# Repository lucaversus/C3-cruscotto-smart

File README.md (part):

# Cruscotto C3+AI

> **Data Logger in standby dal 02/11/2026 fino a nuovo ordine dell'utente (D-064)**, acquisti compresi
> (D1 P6KE33A non si ordina). Stato al blocco: modulo K-line montato e provato a banco (KL-M001, KL-M002);
> materiale arrivato e non montato a disposizione degli altri progetti nel magazzino condiviso.
> **In standby anche la scheda madre del cruscotto** (D-064): carrello svuotato e pezzi riservati liberati.
> Dettagli nel [registro moduli](data-logger/docs/verifiche-moduli.md).

## Fonti del progetto — consultazione obbligatoria

Prima di acquisti, firmware, schemi o collegamenti leggere questa sezione,
[l'inventario hardware](data-logger/docs/hardware-inventory.md),
[lo stato del Data Logger](data-logger/README.md) e la
[procedura di aggiornamento](data-logger/docs/procedura-progetto.md).
Le istruzioni per gli agenti sono in [AGENTS.md](AGENTS.md).
Per iniziare da un clone nuovo, su un altro PC o con un altro agente, seguire
[CONTRIBUTING.md](CONTRIBUTING.md): setup, check e build riproducibili.

L'inventario sorgente è [hardware.json](data-logger/docs/hardware.json);
la vista Markdown è generata per evitare due elenchi divergenti.
Comando prima di decidere e prima di pubblicare:

```powershell
python tools/project_preflight.py
```

## Disegni del progetto

Tutte le tavole e le infografiche, con anteprime, sono nella cartella [`disegni/`](disegni/README.md).

## Biblioteca tecnica della vettura

[Indice dei manuali e ricerca per argomento](docs/manuali/indice.md), rev. 1,
19/10/2026: consultare prima di cercare nuovamente documentazione su diagnosi,
BSI/VAN, quadro, alimentazioni e motore DV4TD. Distingue fonte documentale,
pagina e variante da una misura sul veicolo. Originali e dati personali esclusi da Git.

## Decisioni definitive

Registro iniziale consolidato il **18/10/2026** dalle conferme dell'utente.
Le date indicano la registrazione, non necessariamente la prima discussione.

| ID | Stato | Decisione | Fondamento / vincolo |
| --- | --- | --- | --- |
| D-001 | approvata | Progetto principale **Cruscotto C3+AI**, sottoprogetto **Data Logger**. | Nomi richiesti dall'utente per tutti i cartigli. |
| D-002 | approvata | Sviluppare prima il Data Logger; solo repository **lucaversus/C3-cruscotto-smart**. | Ordine di lavoro e perimetro richiesti. Dal 20/10/2026 l'ordine è aggiornato da D-026 (cruscotto avviato durante la pausa D-025); perimetro invariato. |
| D-003 | approvata | Strumenti software gratuiti, preferibilmente open source; riutilizzare l'hardware disponibile prima di nuovi acquisti. | Vincoli utente; controllare anche moduli non collaudati e in consegna. |
| D-004 | approvata | Registrazione ad **avvio automatico**, senza conferma tramite pulsante. | Utente: “non sono arrivati e facciamola partire in automatico”. |
| D-005 | superata | Inizialmente nessun pulsante richiesto nella prima versione; sostituita da D-015. | Scelta iniziale conservata; il 18/10/2026 l’utente richiede STOP manuale per il logger temporaneo. |
| D-006 | approvata | **Non acquistare CAN Pal o un altro modulo CAN ora**: verificare prima HW-CAN-MCP2515 e HW-CAN-VP230 già disponibili. | Correzione utente: “ma non abbiamo già il modulo can?”. La raccomandazione CAN Pal è ritirata. |
| D-007 | approvata | Lasciare **libera frontalmente la presa OBD**. | Preferenza esplicita utente; soluzione posteriore da identificare, non adattatore già approvato. |
| D-008 | approvata | Non presumere CAN sulla BSI; identificare rete e punto di accesso. Primo ascolto BSI passivo; diagnostica OBD di sola lettura. | Progetto iniziale; aggiornamento 18/10/2026: nuova schermata OBD indica KWP, in conflitto con CAN del Creader. Nessuna delle due identifica la rete BSI. |
| D-009 | approvata | Tutti i documenti visivi di progetto con cornice e cartiglio: progetto, sottoprogetto, titolo, codice, revisione, data, foglio e stato di validazione. | Richiesta esplicita utente; componenti illustrati e fili continui nello schema collegamenti. Dal 20/10/2026 la parte "componenti illustrati" è superata da D-024 (simboli IEC); cornice, cartiglio e fili continui restano validi. |
| D-010 | approvata | Prima fase firmware a banco USB: preservare diagnostica 0.1.0; base 0.2.0 separata, nessuna acquisizione auto finché le interfacce non sono verificate. | 0.1.0 caricata e collaudata; 0.2.0 compilata, non caricata né collaudata sui moduli. |
| D-011 | approvata | Inventario e decisioni versionati, consultati prima di ogni scelta pertinente e aggiornati nello stesso cambiamento. | Richiesta utente del 18/10/2026: non delegare il controllo della memoria all'utente. |
| D-012 | approvata | Archiviare nel repository le foto hardware già disponibili e collegarle all'inventario; consultarle prima di richiederle nuovamente. | Richiesta utente del 18/10/2026. Conservare evidenze e SHA-256, senza metadati personali nelle copie pubblicate. |
| D-013 | approvata | Realizzare in proprio l’interfaccia K-line; prima prototipo e collaudo a banco, poi progetto protetto per auto. | Utente 18/10/2026: “ok procediamo con il circuito autocostruito”. La scelta non certifica lo schema né conferma possesso dei componenti. |
| D-014 | approvata | Escludere il convertitore Pololu dalla distinta acquisti. | Utente 18/10/2026: costo e tempi di invio eccessivi. Eventuali citazioni precedenti restano storiche, non proposte correnti. |
| D-015 | approvata | Data Logger temporaneo per pochi giorni: avvio automatico, pulsante STOP per salvataggio e arresto prima di spegnere l’auto. Nessun UPS o mantenimento automatico richiesto. | Utente 18/10/2026: semplificare lo spin-off; premere il pulsante prima di togliere alimentazione. Conservare limiti elettrici reali e protezione di base. |
| D-016 | approvata | Due sorgenti di acquisizione: diagnostica dalla presa OBD e ascolto passivo della linea dietro al cruscotto originale. Conservare tutti i messaggi ricevuti dalla linea, anche non decodificati, e le risposte OBD di sola lettura, distinguendo le sorgenti. | Utente 18/10/2026: acquisizione tramite OBD e linea dietro al cruscotto, “tutto quello che arriva”. D-007 resta valida; pin e protocollo della linea da verificare. |

| D-017 | approvata | Collegamento temporaneo alla linea dietro al cruscotto con fili volanti fissati e isolati; nessun connettore dedicato da acquistare per questo punto. | Utente 18/10/2026: non interessa il connettore del quadro; identificazione elettrica dei segnali resta necessaria prima del collegamento. |

| D-018 | approvata | Modulo K-line senza jumper JP1 e senza richiamo R3 integrato; resistenza 510 ohm soltanto nel simulatore esterno da banco. | Conferma utente 18/10/2026: collaudare il modulo collegandolo alla linea simulata come alla vettura; nessuna risposta ECU simulata dalla sola resistenza. |

| D-019 | approvata | Usare CR2032 nel RTC e rimuovere la resistenza marcata 201 per interrompere il ramo di ricarica. | Utente 19/10/2026: intervento scelto; eseguito il 20/10/2026 (RTC-M006), ramo interrotto verificato con OL (RTC-M007); confermare interruzione del percorso prima di inserire la pila. Nessuna qualifica hardware dal solo intento. |
| D-020 | approvata | Proseguire con il firmware completo; verifiche tecniche dei moduli a cura dell'utente. Implementare SD/RTC/OLED, STOP D-015, OBD KWP D-013 e ricezione VAN D-008/D-016. | Utente 19/10/2026: "ci penso io alle verifiche". Non equivale a collaudo superato o ad autorizzazione a presumere pin auto. GPIO firmware 0.3.0 documentati come proposti. |
| D-021 | approvata | Controllo di compatibilita a fine blocco, prima di ogni pubblicazione; riscontro decisioni/inventario/configurazioni, check e build quando pertinente. Dopo pubblicazione verificare ref e pipeline sul commit esatto. | Utente 20/10/2026: rendere il controllo una regola. Esecuzione prima di GitHub e conferma CI dopo; non sostituisce collaudi hardware. Build invariata riutilizzabile per sole modifiche documentali, dichiarandolo. |
| D-022 | approvata | Applicare le proposte della revisione del 20/10/2026: firmware 0.3.1 (PID OBD prioritari, pausa KWP ridotta sopra P3min, SPI MicroSD configurabile, predefinita 1 MHz); K-line rev E con isteresi R10; verifiche VAN bloccanti prima del collegamento; prove a banco P-001/P-002 su interruzione e calo di tensione; controllo NVS del backup. | Utente 20/10/2026: "procedere con tutto quello che hai scritto, aggiornando il Git". Non è collaudo: 0.3.1 non caricata, rev E non montata, verifiche VAN e P-001/P-002 non eseguite. D-013, D-015, D-016 restano valide. |
| D-023 | approvata | Qualità del progetto: test C++ host della logica firmware in `dev.py check`, analisi statica cppcheck nella CI (`dev.py lint`), procedure guidate nel repository (`.claude/skills/`: chiusura-blocco, registro-collaudo, revisione-firmware). | Utente 20/10/2026: "Sono d'accordo con quello che hai scritto". Strumenti gratuiti e open source (D-003); procedure nel repository, non sul PC di Luca (AGENTS.md). Non sostituiscono collaudi hardware. |
| D-024 | approvata | Elaborati grafici secondo le norme: simboli IEC 60617, schemi IEC 61082-1, foglio A3 ISO 5457 con zone di riferimento, cartiglio ISO 7200 con tabella revisioni, scrittura ISO 3098, spessori ISO 128. Rifatti KL-001 rev F, EL-003 rev B, EL-001 rev E (storico, sostituito da EL-003) e BL-001 rev D, da una libreria comune `iso_drawing.py`. | Utente 20/10/2026: schemi "non costruiti seguendo le regole ISO", chiede di correggerli tutti. Supera la parte "componenti illustrati" di D-009. Nessuna variazione elettrica: reti, valori e GPIO invariati. |
| D-025 | superata (D-062, 31/10/2026) | Data Logger in pausa dal 20/10/2026 fino a quando il modulo K-line (KL-001) sarà pronto. Alla ripresa: CR2032 da procurare, cablaggio SD (EL-003 rev B) e prima registrazione a banco con prova di mantenimento dell'ora. | Utente 20/10/2026: "al momento metterei in pausa questo progetto secondario", precisato: "finché non avrò pronto il modulo K". Nessuna decisione tecnica modificata; verifiche aperte invariate. |
| D-026 | approvata | Avviare il **Cruscotto digitale** durante la pausa del Data Logger (D-025). Aggiorna l'ordine di lavoro di D-002; perimetro invariato (unico repository). Primo passo: diagnosi della scheda RCmall ESP32-S3 5″ (HW-DASH-DISPLAY) secondo la sezione "Diagnosi all'arrivo della scheda". | Utente 20/10/2026: "voglio iniziare con il progetto del cruscotto"; dichiara di possedere la scheda ("Ce l'ho"). Possesso dichiarato, modello e variante non riscontrati; nessun driver o GPIO fissato. |
| D-027 | approvata | Cruscotto **senza interazione touch**: display dietro la copertura trasparente del quadro; variante ordinata senza touch. Nessun input tattile nella UI. | Utente 20/10/2026: "l'ho ordinato non touch perché tanto andrà dietro la copertura trasparente del cruscotto e non ci sarà modo di interagire con il tocco". Comandi eventuali (es. cambio pagina) da definire separatamente. |
| D-028 | approvata | Messaggi audio dell'IA dall'S3 sugli altoparlanti dell'auto tramite **relè di commutazione**: a riposo altoparlanti collegati alla radio originale; durante il messaggio il relè li collega all'uscita audio dell'S3 (radio di fatto in muto). Funziona anche a radio spenta; nessun comando trasmesso sul VAN. | Utente 20/10/2026: messaggi "anche con radio spenta e in caso di radio accesa quest'ultima messa in muto"; "io avevo pensato alla proposta A, l'auto è quella originale". Amplificatore, relè, canali e altoparlanti da definire; uscite radio a ponte da non collegare a massa. |
| D-029 | approvata | Architettura del cruscotto a **due microcontrollori**: un ESP32 **front-end** legge VAN (solo ricezione) e K-line e inoltra all'S3 dati compatti su UART a 2 fili; l'ESP32-S3 8048S050 gestisce display, IA, audio e relè, senza collegamenti diretti al veicolo. Prototipo con HW-ESP32 (HW-394) e moduli presenti; obiettivo finale una **scheda madre** dietro l'S3 con modulo ESP32-WROOM-32E senza PSRAM (N8 o N16: la PSRAM occupa GPIO16/17), protezioni 12 V, convertitore 5 V, interfacce VAN/K-line, relè audio e **connettore multipolare** verso l'auto. | Utente 20/10/2026: "allora passiamo a questa nuova architettura"; obiettivo scheda madre con "connettore multipolo per rendere il collegamento con l'auto più solido e di veloce e pulita installazione". Stesso hardware e codice tra raccolta dati e uso (dataset IA coerente). Nessun acquisto ordinato; GPIO S3 e protocollo UART da definire. |
| D-030 | approvata | Alimentazione del cruscotto da **+12 V permanente con ingresso chiave**: accensione con la chiave (in futuro anche ad altri eventi), mantenimento di qualche secondo dopo lo spegnimento per salvare lo stato, poi autospegnimento; consumo a riposo da contenere (obiettivo indicativo < 1 mA). Avviamento superato con **condensatore di riserva sulla scheda madre**. Protezioni: fusibile, inversione polarità, TVS, filtro, massa comune con il quadro. | Utente 20/10/2026: "1.B e 2. condensatore lo vedo come più facile installare nella mainboard". Non sostituisce D-015 per il logger temporaneo. Calo reale all'avviamento, durata e capacità del condensatore da misurare/calcolare; punto di prelievo +12 V e segnale chiave da identificare. |
| D-031 | approvata | **Raffreddamento attivo** del cruscotto: dissipatore in alluminio dietro l'S3 e **ventola 12 V** predisposta nelle staffe stampate, pilotata in PWM dal front-end. Funziona anche a **motore spento** finché la batteria a riposo resta sopra una **soglia di guardia (partenza 12,3 V)**, con isteresi e tempo massimo; scheda madre con **dominio sempre acceso** a basso consumo (front-end in sonno, NTC, misura batteria, ventola) separato dal dominio principale 5 V/S3. Sensori NTC vicino al display. | Utente 21/10/2026: "predisporrei immediatamente una ventola e applicherò un dissipatore in alluminio dietro il modulo S3", "se la ventola sarebbe possibile farla funzionare da macchina spenta fino ad un livello della batteria di guardia studiamolo"; conferma "procedi". Limiti pannello dichiarati dal rivenditore −20…+70 °C (magazzinaggio +80 °C). Soglie da tarare; efficacia da misurare la prossima estate. |
| D-032 | approvata | **VIN nei dati grezzi VAN** (IDEN E24 secondo le decodifiche comunitarie): il logger continua a registrare tutto senza filtri (D-016); il VIN va **mascherato solo prima di pubblicare o condividere** i dati, in post-elaborazione. Gli originali con VIN restano solo in locale, esclusi da Git. | Utente 21/10/2026, alla questione A della revisione generale: "mascheriamolo solo prima della pubblicazione". Strumento di mascheramento da realizzare prima della prima pubblicazione di dati; nessuna modifica al firmware. |
| D-033 | approvata | **Stessi canali nel Data Logger e nel front-end**: oltre a VAN e K-line il logger registra IMU (HW-IMU-LSM6DSO; fino al 22/10/2026 indicato HW-IMU-LSM6DS3), tensione batteria, segnale chiave e temperature NTC, con gli stessi sensori, montaggi e frequenze previsti per il cruscotto, così che il dataset di addestramento corrisponda ai dati disponibili in uso. Fonti di dati aggiuntive per l'IA da valutare (questioni aperte). | Utente 21/10/2026, questione B della revisione: "assolutamente sì, anzi pensa possiamo dare in pasto altri dati all'AI". Firmware logger, schema EL-003 e GPIO del logger da aggiornare; nessun collegamento eseguito. |
| D-034 | approvata | Licenza del repository **MIT** per codice, documenti e disegni del progetto; file `LICENSE` nella radice. Codice di terzi con la propria licenza (THIRD_PARTY.md); manuali e dati personali esclusi. Evitare librerie GPL nel firmware distribuito. | Utente 21/10/2026: "il progetto per me è totalmente open, chiunque vuole può utilizzarlo"; "ok mit". |
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
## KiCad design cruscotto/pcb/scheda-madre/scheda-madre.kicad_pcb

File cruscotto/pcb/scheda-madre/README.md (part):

# Scheda madre — circuito stampato (KiCad 10)

Progetto KiCad della scheda madre del cruscotto (D-029, D-044, D-045, D-046). Stato:
circuito stampato con la **sola meccanica**; schema elettrico iniziato con il foglio
**alimentazione** (C3AI-CR-EL-001 rev C), **front-end** (C3AI-CR-EL-002 rev A, `front-end.kicad_sch`) e
**interfacce veicolo** (C3AI-CR-EL-003 rev B, `interfacce-veicolo.kicad_sch`) e **sensori e memoria**
(C3AI-CR-EL-004 rev B, `sensori-memoria.kicad_sch`) e **collegamento S3 e audio** (C3AI-CR-EL-005
rev A, `s3-audio.kicad_sch`), proposte non verificate.

- `scheda-madre.kicad_pcb`: generato da `tools/genera-pcb-scheda-madre.py` con il Python di
  KiCad. Contiene il bordo letto dal DXF dell'utente (`cruscotto/meccanica/scheda-madre-contorno.dxf`),
  il foro Ø38 della ventola, 6 fori di fissaggio Ø3 senza rame, 4 fori Ø3,2 della ventola
  40 × 40, gli interruttori S1/S2 (tattili 6 × 6 alti 7,3 mm) sotto i pulsanti originali e il
  connettore J1 Micro-Fit 2×12 orizzontale sul retro, con il fronte al bordo inferiore.
  S1/S2 centrati sotto i pulsanti e ruotati di ±111° (piedini paralleli al bordo): i piedini
  rispettano 0,5 mm dal bordo, gli angoli dell'ingombro del corpo sporgono di circa 0,5 mm. Su
  User.Drawings il contorno della S3, su User.Comments le zone dello studio C3AI-CR-PL-001.
- `scheda-madre.kicad_sch`: generato da `tools/genera-schema-scheda-madre.py` (Python normale)
  con i simboli delle librerie di KiCad 10. Collegamenti disegnati con fili dentro ogni blocco,
  etichette solo per le reti verso altri blocchi o fogli. Il generatore confronta il netlist
  esportato da KiCad con le reti volute e si ferma a ogni differenza. Etichette globali: valgono in tutti i fogli. ERC: 0 errori,
  1 avviso per la massa di riferimento VAN (J1 via 7) ancora da collegare. Anteprima in `disegni/CR-EL-001_scheda-madre-alimentazione.png`.
- `scheda-madre.pretty/` con `fp-lib-table`: impronte del progetto non presenti nelle librerie
  standard, per ora `ST_DIL24_Adapter_W15.0mm` (adattatore ST DIL24, interasse 15,0 mm).
- Faccia **F** = faccia interna verso la S3 (componenti caldi, interruttori); **B** = retro
  (ventola, J1).
- Regole: 4 strati (D-057: F e B componenti e piste, In1 piano di massa continuo, In2 piste e massa),
  1,6 mm, distanza minima 0,2 mm, pista minima 0,15 mm, via 0,6/0,3, 0,3 mm dal bordo; regola di progetto
  `scheda-madre.kicad_dru` (un raggio di raccordo termico basta sui fori passanti, massa garantita da In1);
  montaggio a mano, si produce solo il circuito stampato (D-046).

Rigenerare:

```text
python tools/genera-schema-scheda-madre.py
"C:\Program Files\KiCad\10.0\bin\kicad-cli.exe" sch erc cruscotto/pcb/scheda-madre/scheda-madre.kicad_sch
"C:\Program Files\KiCad\10.0\bin\python.exe" tools/genera-pcb-scheda-madre.py
"C:\Program Files\KiCad\10.0\bin\kicad-cli.exe" pcb drc cruscotto/pcb/scheda-madre/scheda-madre.kicad_pcb
```

Le modifiche fatte a mano in KiCad sugli elementi generati si perdono rigenerando: la rigenerazione
rifà piazzamento e sbroglio da capo (sezione «Sbroglio completo» qui sotto).

## Piazzamento preliminare (25/10/2026)

Il generatore legge il netlist dello schema con `kicad-cli`, assegna le reti ai piedini e
dispone tutti i 139 componenti per blocchi, controllando contorno, fori (zona libera di
3,2 mm oltre il foro), foro e corpo della ventola, sovrapposizioni e, per i componenti a foro
passante, entrambe le facce. Anteprime: `piazzamento-lato-F.png` (faccia interna verso la
S3) e `piazzamento-lato-B.png` (retro, vista speculare).

- Faccia F (altezza massima circa 8 mm, distanza dalla S3 ~9,9 mm): alimentazione con le
  parti calde accanto alla ventola a sinistra (D-046), front-end ESP32 a destra, USB-C e
  CH340C al bordo superiore libero dalla S3, K-line e VAN, cavetti J10-J12 verso la S3.
- Faccia B: relè K1/K2, zoccolo dell'IMU J6, modulo VAN (J8/J9), RTC con portapila (pila
  sostituibile dal retro), condensatore C3, connettore della ventola J4, J1 verso l'auto.
- Modulo ESP32: radio non usata (D-029, D-036), quindi courtyard sul solo corpo e nessuna
  zona vietata d'antenna; fori termici da 0,2 mm sotto la piazzola di massa.
- Regole nel file di progetto `scheda-madre.kicad_pro` (foro minimo 0,2 mm per i fori termici).

**Orientamento:** il DXF dell'utente descrive la scheda vista dal retro, KiCad la disegna vista
dalla faccia F (verso la S3): le x sono speculari. Per i pezzi legati alla S3 vale x(KiCad) =
−x(assieme): J10 (P1), J12 (Speak) e J11 (P2) stanno quindi a x negative. Per inserire il modello 3D
esportato (`kicad-cli pcb export step --subst-models --user-origin 148.5x151mm`) nell'assieme:
rotazione di 180° attorno all'asse y, poi traslazione (0, 12, 23,6) mm.

**Altezze (25/10/2026, modello 3D di KiCad e tft-5inch.step):** sulla faccia F il componente più
critico è C29 (5,4 mm) con 5,5 mm di spazio residuo verso i componenti della S3; poi L1 (6,0 mm,
6,2 mm residui). Dal 27/10/2026 (D-059) J4, J5 e J10-J12 sono piazzole per fili saldati: il filo verso la
S3 va piegato parallelo alla scheda (spazio di circa 9,9 mm). Sul retro i più alti sono i relè K1/K2 (15,7 mm), C3
(10,1 mm), le file di pin del modulo VAN (8,7 mm) e J1 con la spina: profondità disponibile
dietro la scheda madre da misurare (verifica aperta 1 in `cruscotto/docs/scheda-madre.md`). Senza modello 3D in KiCad: U2, J1, J3, J10-J12, K1/K2
(altezze dalle schede tecniche).

DRC del 25/10/2026: nessun errore oltre ai 325 collegamenti non ancora tracciati (sbroglio da
fare). Da rivedere prima dello sbroglio: interasse delle file di pin del modulo VAN, profondità
dietro la scheda, posizione fine dei gruppi (piazzamento automatico, non ottimizzato per le piste).

## Sbroglio automatico, prima stesura (25/10/2026)

`tools/sbroglia-scheda-madre.py` (Python di KiCad): classi di rete (Potenza 1,0 mm, Medio 0,5 mm,
segnali 0,25 mm), piani di massa sulle due facce, esportazione Specctra, Freerouting 2.5.0 su Java 25
portatile (la versione CLI nativa per Windows si blocca), importazione e riempimento dei piani.
Esito con 25 passate (circa 30 minuti): 1617 piste e 210 via, **71 connessioni non tracciate**
secondo Freerouting; DRC: 108 elementi non connessi (comprese isole del piano di massa), 187 tratti
sotto 0,2 mm vicino alle piazzole, 36 piste troppo vicine al foro della ventola (Freerouting non
vede il foro come bordo), 34 raccordi termici incompleti. Anteprime `sbroglio-rame-F.png` e
`sbroglio-rame-B.png` (superate). **Non utilizzabile così**: serve un piazzamento più raccolto per gruppo e
una zona vietata attorno al foro della ventola, poi un nuovo sbroglio.

## Sbroglio completo a 4 strati (26/10/2026)

Con due strati Freerouting si fermava a 28-32 connessioni aperte; la scheda passa a 4 strati (D-057).
Lo spostamento della ventola verso il centro della S3 (D-058) è stato provato e scartato: peggiorava lo
sbroglio (46 connessioni aperte).

Procedura (Python di KiCad; Freerouting e Java come sopra):

```text
"C:\Program Files\KiCad\10.0\bin\python.exe" tools/genera-pcb-scheda-madre.py
"C:\Program Files\KiCad\10.0\bin\python.exe" tools/sbroglia-scheda-madre.py <java.exe> <freerouting.jar> 40
"C:\Program Files\KiCad\10.0\bin\python.exe" tools/completa-sbroglio-scheda-madre.py
"C:\Program Files\KiCad\10.0\bin\python.exe" tools/serigrafia-scheda-madre.py
"C:\Program Files\KiCad\10.0\bin\python.exe" tools/modelli-3d-scheda-madre.py
```

1. `sbroglia-scheda-madre.py`: classi di rete (Potenza 0,8 mm, 5V 0,6 mm, Medio 0,3 mm, segnali 0,2 mm),
   riempimenti di massa su F, In1 e B, In1 dichiarato strato di alimentazione nel file Specctra (niente piste,
   piano continuo), Freerouting con 40 passate (si ferma da solo dopo 10 passate senza miglioramenti),
   massa anche su In2, via di cucitura ogni 4 mm. Esito: 27-31 connessioni aperte. Freerouting usa limiti di
   tempo interni: due esecuzioni sullo stesso piazzamento danno risultati leggermente diversi.
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
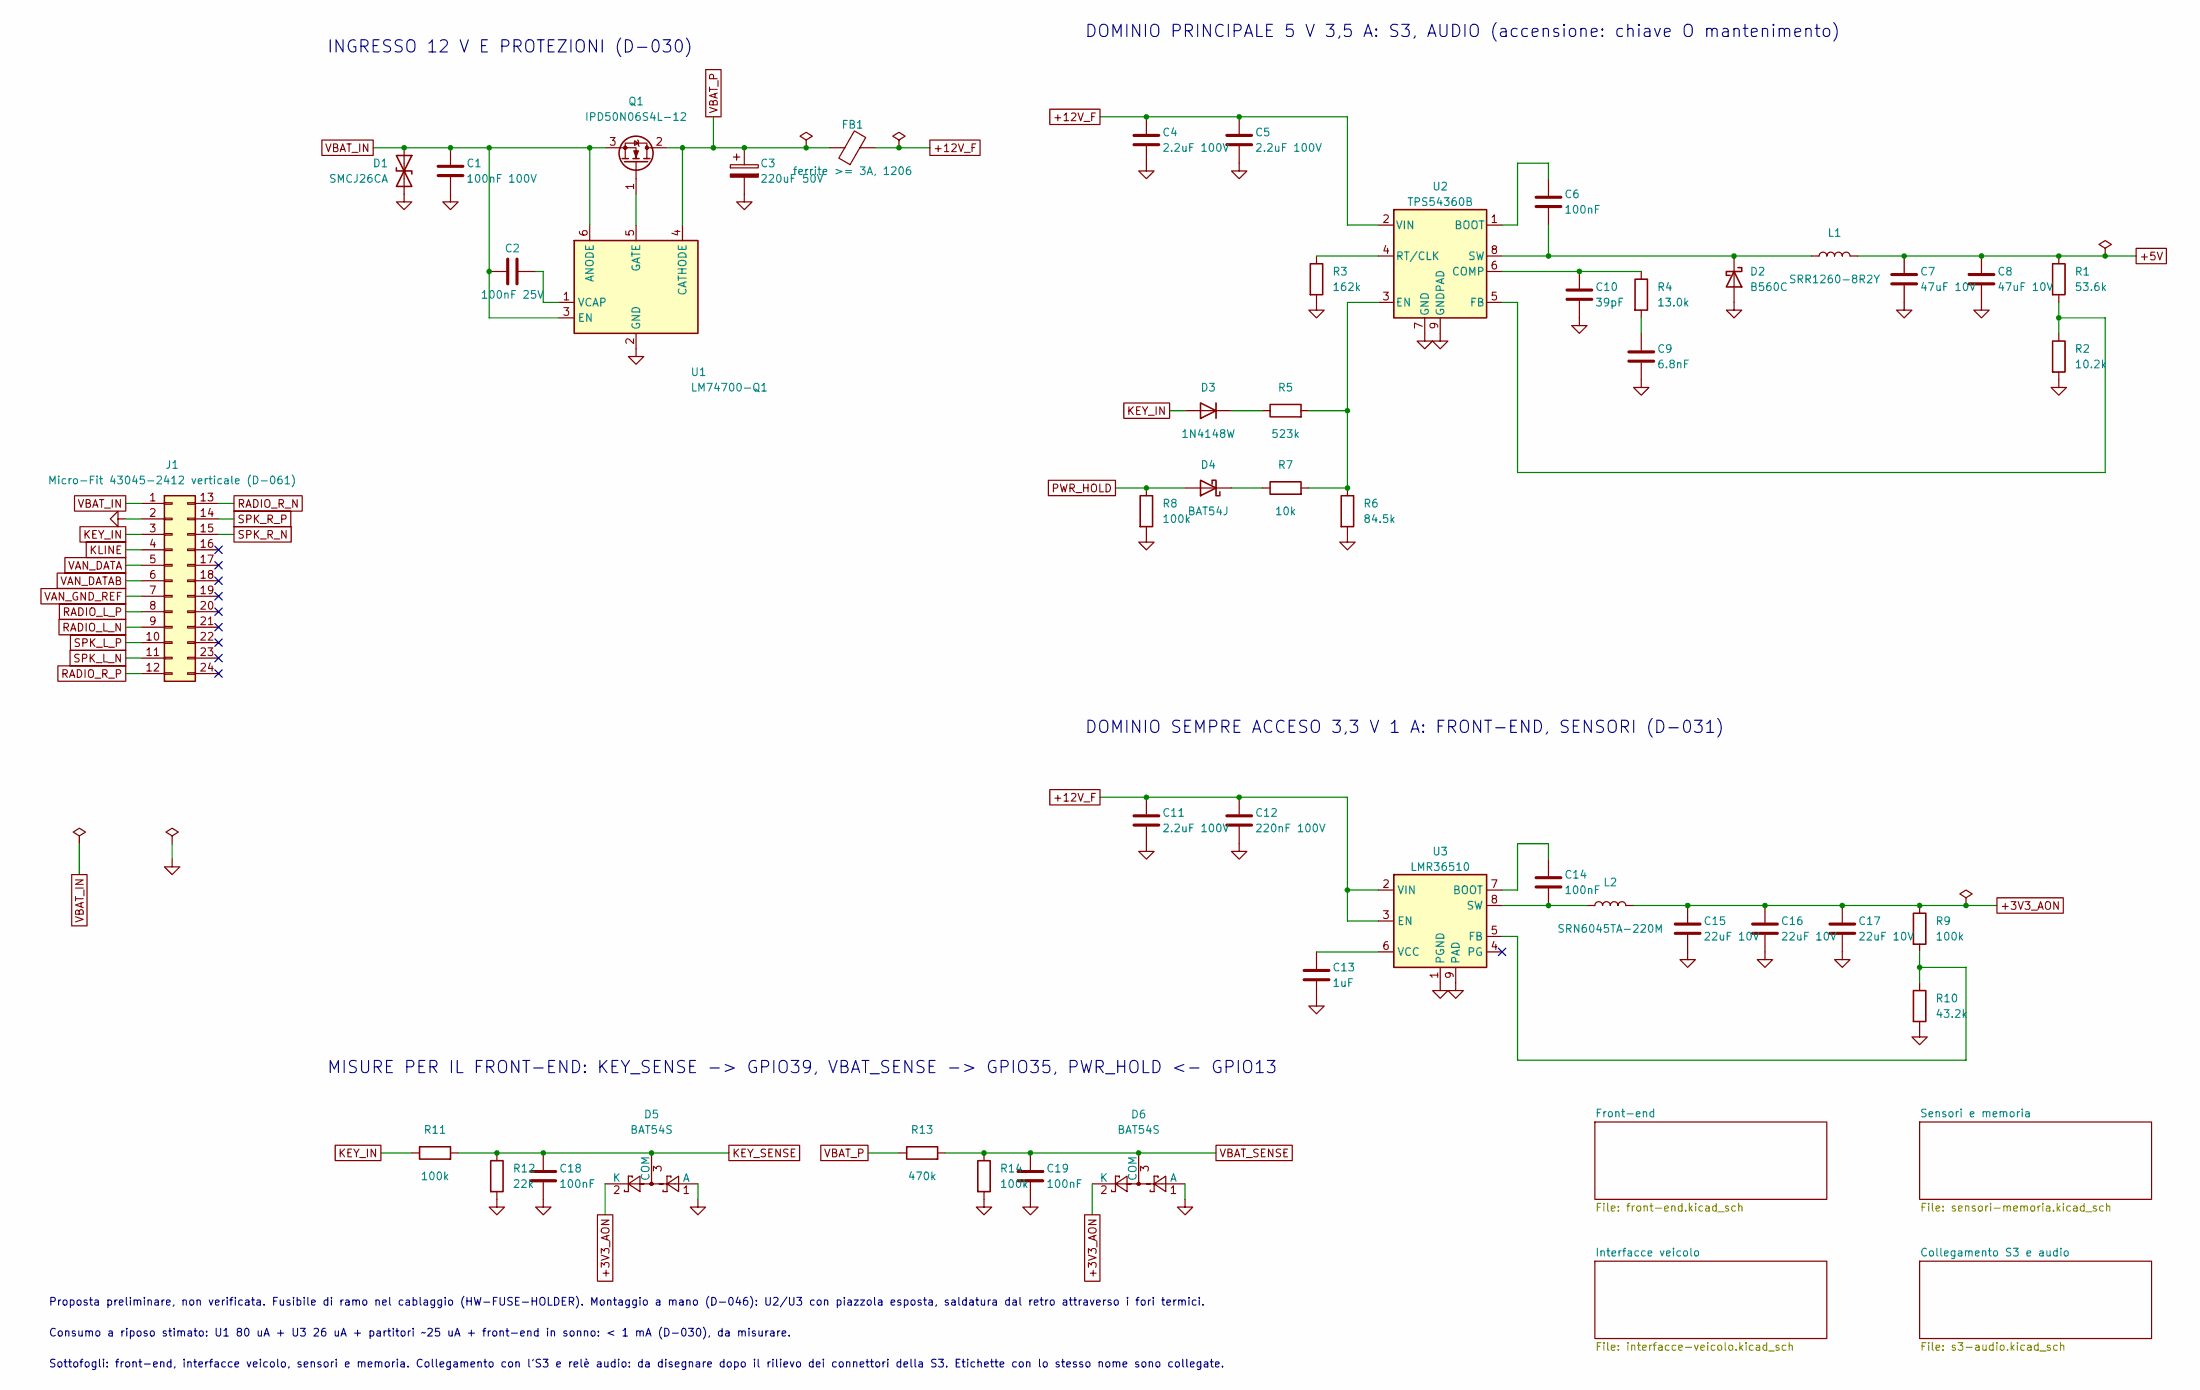
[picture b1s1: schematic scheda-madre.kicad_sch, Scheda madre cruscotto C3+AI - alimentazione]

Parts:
C1: 100nF 100V; C_0805_2012Metric_Pad1.18x1.45mm_HandSolder
C2: 100nF 25V; C_0805_2012Metric_Pad1.18x1.45mm_HandSolder
C3: 220uF 50V; CP_Radial_D10.0mm_P5.00mm
C4, C5, C11: 2.2uF 100V; C_1210_3225Metric_Pad1.33x2.70mm_HandSolder
C6, C14, C18, C19: 100nF; C_0805_2012Metric_Pad1.18x1.45mm_HandSolder
C7, C8: 47uF 10V; C_1210_3225Metric_Pad1.33x2.70mm_HandSolder
C9: 6.8nF; C_0805_2012Metric_Pad1.18x1.45mm_HandSolder
C10: 39pF; C_0805_2012Metric_Pad1.18x1.45mm_HandSolder
C12: 220nF 100V; C_0805_2012Metric_Pad1.18x1.45mm_HandSolder
C13: 1uF; C_0805_2012Metric_Pad1.18x1.45mm_HandSolder
C15, C16, C17: 22uF 10V; C_1206_3216Metric_Pad1.33x1.80mm_HandSolder
D1: SMCJ26CA; D_SMC
D2: B560C; D_SMC
D3: 1N4148W; D_SOD-123
D4: BAT54J; D_SOD-323F
D5, D6: BAT54S; SOT-23
FB1: ferrite >= 3A, 1206; L_1206_3216Metric_Pad1.22x1.90mm_HandSolder
J1: Micro-Fit 43045-2412 verticale (D-061); Molex_Micro-Fit_3.0_43045-2412_2x12_P3.00mm_Vertical
L1: SRR1260-8R2Y; L_Bourns_SRR1260
L2: SRN6045TA-220M; L_Bourns_SRN6045TA
Q1: IPD50N06S4L-12; TO-252-2
R1: 53.6k; R_0805_2012Metric_Pad1.20x1.40mm_HandSolder
R2: 10.2k; R_0805_2012Metric_Pad1.20x1.40mm_HandSolder
R3: 162k; R_0805_2012Metric_Pad1.20x1.40mm_HandSolder
R4: 13.0k; R_0805_2012Metric_Pad1.20x1.40mm_HandSolder
R5: 523k; R_0805_2012Metric_Pad1.20x1.40mm_HandSolder
R6: 84.5k; R_0805_2012Metric_Pad1.20x1.40mm_HandSolder
R7: 10k; R_0805_2012Metric_Pad1.20x1.40mm_HandSolder
R8, R9, R11, R14: 100k; R_0805_2012Metric_Pad1.20x1.40mm_HandSolder
R10: 43.2k; R_0805_2012Metric_Pad1.20x1.40mm_HandSolder
R12: 22k; R_0805_2012Metric_Pad1.20x1.40mm_HandSolder
R13: 470k; R_0805_2012Metric_Pad1.20x1.40mm_HandSolder
U1: LM74700-Q1; SOT-23-6
U2: TPS54360B; TI_SO-PowerPAD-8_ThermalVias
U3: LMR36510; Texas_HTSOP-8-1EP_3.9x4.9mm_P1.27mm_EP2.95x4.9mm_Mask2.4x3.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

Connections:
+3V3_AON: C15.1, C16.1, C17.1, D5.2 (K), D6.2 (K), L2.2, R9.1; also elsewhere on the board
+5V: C7.1, C8.1, L1.2, R1.1; also elsewhere on the board
+12V_F: C4.1, C5.1, C11.1, C12.1, FB1.2, U2.2 (VIN), U3.2 (VIN), U3.3 (EN); also elsewhere on the board
GND: C1.2, C3.2, C4.2, C5.2, C7.2, C8.2, C9.2, C10.2, C11.2, C12.2, C13.2, C15.2, C16.2, C17.2, C18.2, C19.2, D1.2 (A2), D2.2 (A), D5.1 (A), D6.1 (A), J1.2, R2.2, R3.2, R6.2, R8.2, R10.2, R12.2, R14.2, U1.2 (GND), U2.7 (GND), U2.9 (GNDPAD), U3.1 (PGND), U3.9 (PAD); also elsewhere on the board
KEY_IN: D3.2 (A), J1.3, R11.1; also elsewhere on the board
KEY_SENSE: C18.1, D5.3 (COM), R11.2, R12.1; also elsewhere on the board
KLINE: J1.4; also elsewhere on the board
unnamed: C9.1, R4.2
unnamed: C6.2, D2.1 (K), L1.1, U2.8 (SW)
unnamed: D3.1 (K), R5.1
unnamed: D4.1 (K), R7.1
unnamed: Q1.1 (G), U1.5 (GATE)
unnamed: C2.2, U1.1 (VCAP)
unnamed: C6.1, U2.1 (BOOT)
unnamed: C10.1, R4.1, U2.6 (COMP)
unnamed: R5.2, R6.1, R7.2, U2.3 (EN)
unnamed: R1.2, R2.1, U2.5 (FB)
unnamed: R3.1, U2.4 (RT/CLK)
unnamed: C14.1, U3.7 (BOOT)
unnamed: R9.2, R10.1, U3.5 (FB)
unnamed: C14.2, L2.1, U3.8 (SW)
unnamed: C13.1, U3.6 (VCC)
PWR_HOLD: D4.2 (A), R8.1; also elsewhere on the board
RADIO_L_N: J1.9; also elsewhere on the board
RADIO_L_P: J1.8; also elsewhere on the board
RADIO_R_N: J1.13; also elsewhere on the board
RADIO_R_P: J1.12; also elsewhere on the board
SPK_L_N: J1.11; also elsewhere on the board
SPK_L_P: J1.10; also elsewhere on the board
SPK_R_N: J1.15; also elsewhere on the board
SPK_R_P: J1.14; also elsewhere on the board
VAN_DATA: J1.5; also elsewhere on the board
VAN_DATAB: J1.6; also elsewhere on the board
VAN_GND_REF: J1.7
VBAT_IN: C1.1, C2.1, D1.1 (A1), J1.1, Q1.3 (S), U1.3 (EN), U1.6 (ANODE)
VBAT_P: C3.1, FB1.1, Q1.2 (D), R13.1, U1.4 (CATHODE)
VBAT_SENSE: C19.1, D6.3 (COM), R13.2, R14.1; also elsewhere on the board

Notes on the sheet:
INGRESSO 12 V E PROTEZIONI (D-030)
DOMINIO PRINCIPALE 5 V 3,5 A: S3, AUDIO (accensione: chiave O mantenimento)
DOMINIO SEMPRE ACCESO 3,3 V 1 A: FRONT-END, SENSORI (D-031)
MISURE PER IL FRONT-END: KEY_SENSE -> GPIO39, VBAT_SENSE -> GPIO35, PWR_HOLD <- GPIO13
Proposta preliminare, non verificata. Fusibile di ramo nel cablaggio (HW-FUSE-HOLDER). Montaggio a mano (D-046): U2/U3 con piazzola esposta, saldatura dal retro attraverso i fori termici.
Consumo a riposo stimato: U1 80 uA + U3 26 uA + partitori ~25 uA + front-end in sonno: < 1 mA (D-030), da misurare.
Sottofogli: front-end, interfacce veicolo, sensori e memoria. Collegamento con l’S3 e relè audio: da disegnare dopo il rilievo dei connettori della S3. Etichette con lo stesso nome sono collegate.

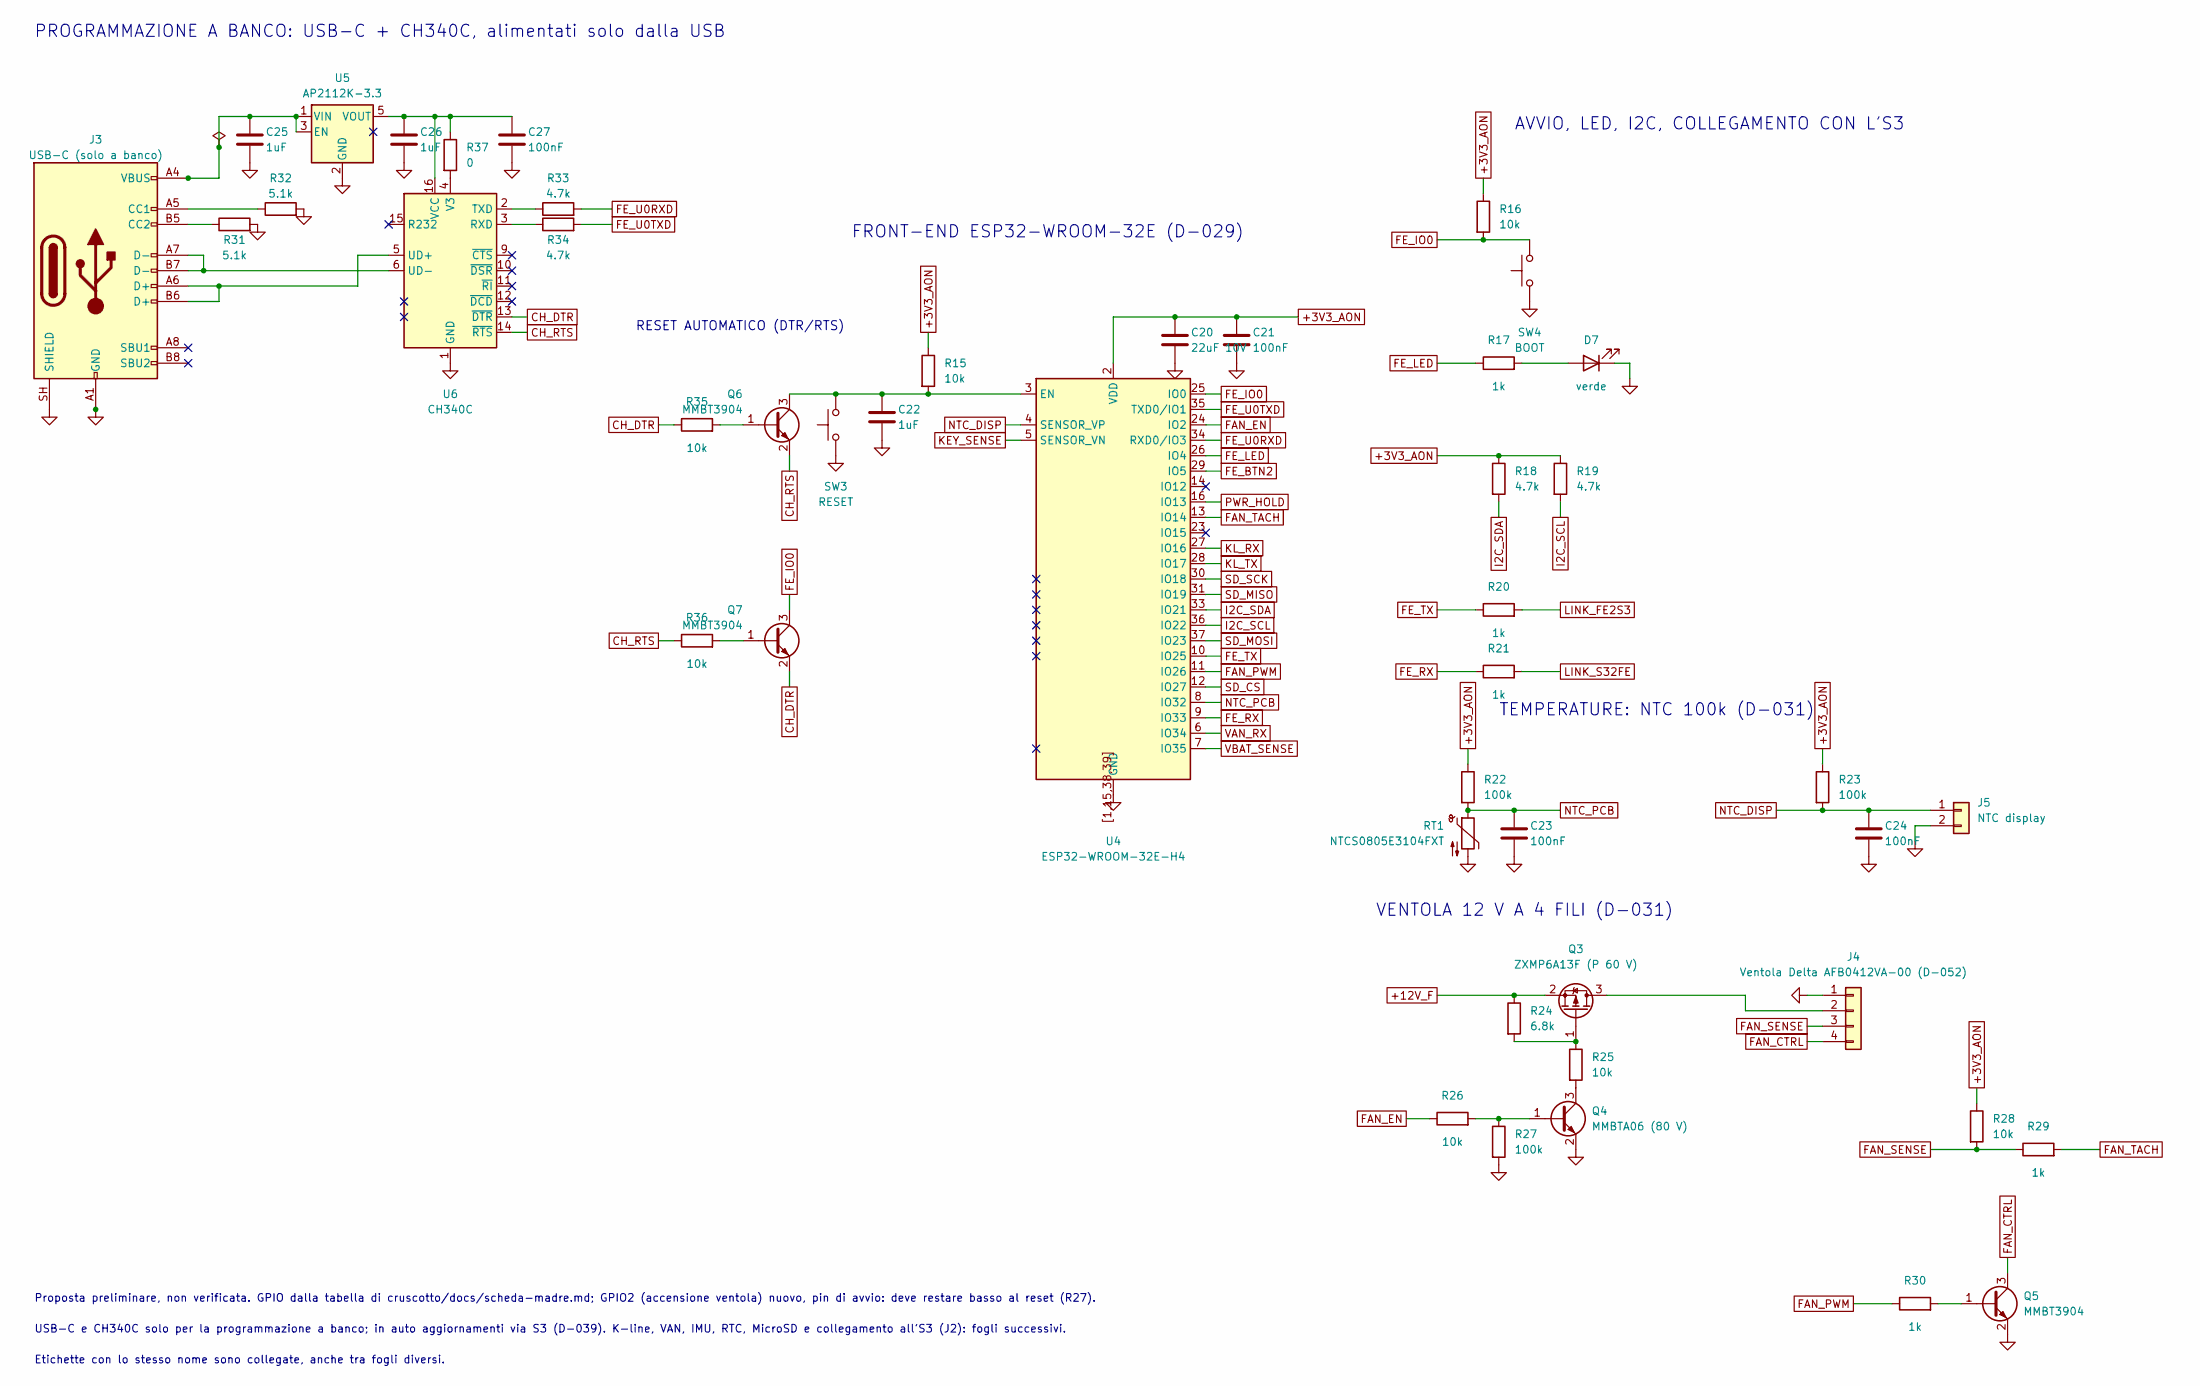
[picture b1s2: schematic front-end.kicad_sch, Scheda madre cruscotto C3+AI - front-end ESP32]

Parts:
C20: 22uF 10V; C_1206_3216Metric_Pad1.33x1.80mm_HandSolder
C21, C23, C24, C27: 100nF; C_0805_2012Metric_Pad1.18x1.45mm_HandSolder
C22, C25, C26: 1uF; C_0805_2012Metric_Pad1.18x1.45mm_HandSolder
D7: verde; LED_0805_2012Metric_Pad1.15x1.40mm_HandSolder
J3: USB-C (solo a banco); USB_C_Receptacle_HRO_TYPE-C-31-M-12
J4: Ventola Delta AFB0412VA-00 (D-052); SolderWire-0.127sqmm_1x04_P3.7mm_D0.48mm_OD1mm
J5: NTC display; SolderWire-0.127sqmm_1x02_P3.7mm_D0.48mm_OD1mm
Q3: ZXMP6A13F (P 60 V); SOT-23
Q4: MMBTA06 (80 V); SOT-23
Q5, Q6, Q7: MMBT3904; SOT-23
R15, R16, R25, R26, R28, R35, R36: 10k; R_0805_2012Metric_Pad1.20x1.40mm_HandSolder
R17, R20, R21, R29, R30: 1k; R_0805_2012Metric_Pad1.20x1.40mm_HandSolder
R18, R19, R33, R34: 4.7k; R_0805_2012Metric_Pad1.20x1.40mm_HandSolder
R22, R23, R27: 100k; R_0805_2012Metric_Pad1.20x1.40mm_HandSolder
R24: 6.8k; R_0805_2012Metric_Pad1.20x1.40mm_HandSolder
R31, R32: 5.1k; R_0805_2012Metric_Pad1.20x1.40mm_HandSolder
R37: 0; R_0805_2012Metric_Pad1.20x1.40mm_HandSolder
RT1: NTCS0805E3104FXT; R_0805_2012Metric_Pad1.20x1.40mm_HandSolder
SW3: RESET; SW_PUSH_6mm
SW4: BOOT; SW_PUSH_6mm
U4: ESP32-WROOM-32E-H4; ESP32-WROOM-32E
U5: AP2112K-3.3; SOT-23-5
U6: CH340C; SOIC-16_3.9x9.9mm_P1.27mm

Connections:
+3V3_AON: C20.1, C21.1, R15.1, R16.1, R18.1, R19.1, R22.1, R23.1, R28.1, U4.2 (VDD); also elsewhere on the board
+12V_F: Q3.2 (S), R24.1; also elsewhere on the board
CH_DTR: Q7.2 (E), R35.1, U6.13 (~DTR)
CH_RTS: Q6.2 (E), R36.1, U6.14 (~RTS)
FAN_CTRL: J4.4, Q5.3 (C)
FAN_EN: R26.1, U4.24 (IO2)
FAN_PWM: R30.1, U4.11 (IO26)
FAN_SENSE: J4.3, R28.2, R29.1
FAN_TACH: R29.2, U4.13 (IO14)
FE_BTN2: U4.29 (IO5); also elsewhere on the board
FE_IO0: Q7.3 (C), R16.2, SW4.2, U4.25 (IO0)
FE_LED: R17.1, U4.26 (IO4)
FE_RX: R21.1, U4.9 (IO33)
FE_TX: R20.1, U4.10 (IO25)
FE_U0RXD: R33.2, U4.34 (RXD0/IO3)
FE_U0TXD: R34.2, U4.35 (TXD0/IO1)
GND: C20.2, C21.2, C22.2, C23.2, C24.2, C25.2, C26.2, C27.2, D7.1 (K), J3.A1 (GND), J3.A12 (GND), J3.B1 (GND), J3.B12 (GND), J3.SH (SHIELD), J4.1, J5.2, Q4.2 (E), Q5.2 (E), R27.2, R31.2, R32.2, RT1.2, SW3.1, SW4.1, U4.1, U4.15, U4.38, U4.39, U4.[1,15,38,39] (GND), U5.2 (GND), U6.1 (GND); also elsewhere on the board
I2C_SCL: R19.2, U4.36 (IO22); also elsewhere on the board
I2C_SDA: R18.2, U4.33 (IO21); also elsewhere on the board
KEY_SENSE: U4.5 (SENSOR_VN); also elsewhere on the board
KL_RX: U4.27 (IO16); also elsewhere on the board
KL_TX: U4.28 (IO17); also elsewhere on the board
LINK_FE2S3: R20.2; also elsewhere on the board
LINK_S32FE: R21.2; also elsewhere on the board
NTC_DISP: C24.1, J5.1, R23.2, U4.4 (SENSOR_VP)
NTC_PCB: C23.1, R22.2, RT1.1, U4.8 (IO32)
unnamed: D7.2 (A), R17.2
unnamed: J3.A5 (CC1), R32.1
unnamed: J3.B5 (CC2), R31.1
unnamed: J4.2, Q3.3 (D)
unnamed: Q3.1 (G), R24.2, R25.1
unnamed: Q4.1 (B), R26.2, R27.1
unnamed: Q4.3 (C), R25.2
unnamed: Q5.1 (B), R30.2
unnamed: Q6.1 (B), R35.2
unnamed: C22.1, Q6.3 (C), R15.2, SW3.2, U4.3 (EN)
unnamed: Q7.1 (B), R36.2
unnamed: C25.1, J3.A4 (VBUS), J3.A9 (VBUS), J3.B4 (VBUS), J3.B9 (VBUS), U5.1 (VIN), U5.3 (EN)
unnamed: C26.1, C27.1, R37.1, U5.5 (VOUT), U6.16 (VCC)
unnamed: R34.1, U6.3 (RXD)
unnamed: R33.1, U6.2 (TXD)
unnamed: J3.A6 (D+), J3.B6 (D+), U6.5 (UD+)
unnamed: J3.A7 (D-), J3.B7 (D-), U6.6 (UD-)
unnamed: R37.2, U6.4 (V3)
PWR_HOLD: U4.16 (IO13); also elsewhere on the board
SD_CS: U4.12 (IO27); also elsewhere on the board
SD_MISO: U4.31 (IO19); also elsewhere on the board
SD_MOSI: U4.37 (IO23); also elsewhere on the board
SD_SCK: U4.30 (IO18); also elsewhere on the board
VAN_RX: U4.6 (IO34); also elsewhere on the board
VBAT_SENSE: U4.7 (IO35); also elsewhere on the board

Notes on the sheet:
PROGRAMMAZIONE A BANCO: USB-C + CH340C, alimentati solo dalla USB
RESET AUTOMATICO (DTR/RTS)
FRONT-END ESP32-WROOM-32E (D-029)
AVVIO, LED, I2C, COLLEGAMENTO CON L'S3
TEMPERATURE: NTC 100k (D-031)
VENTOLA 12 V A 4 FILI (D-031)
Proposta preliminare, non verificata. GPIO dalla tabella di cruscotto/docs/scheda-madre.md; GPIO2 (accensione ventola) nuovo, pin di avvio: deve restare basso al reset (R27).
USB-C e CH340C solo per la programmazione a banco; in auto aggiornamenti via S3 (D-039). K-line, VAN, IMU, RTC, MicroSD e collegamento all'S3 (J2): fogli successivi.
Etichette con lo stesso nome sono collegate, anche tra fogli diversi.

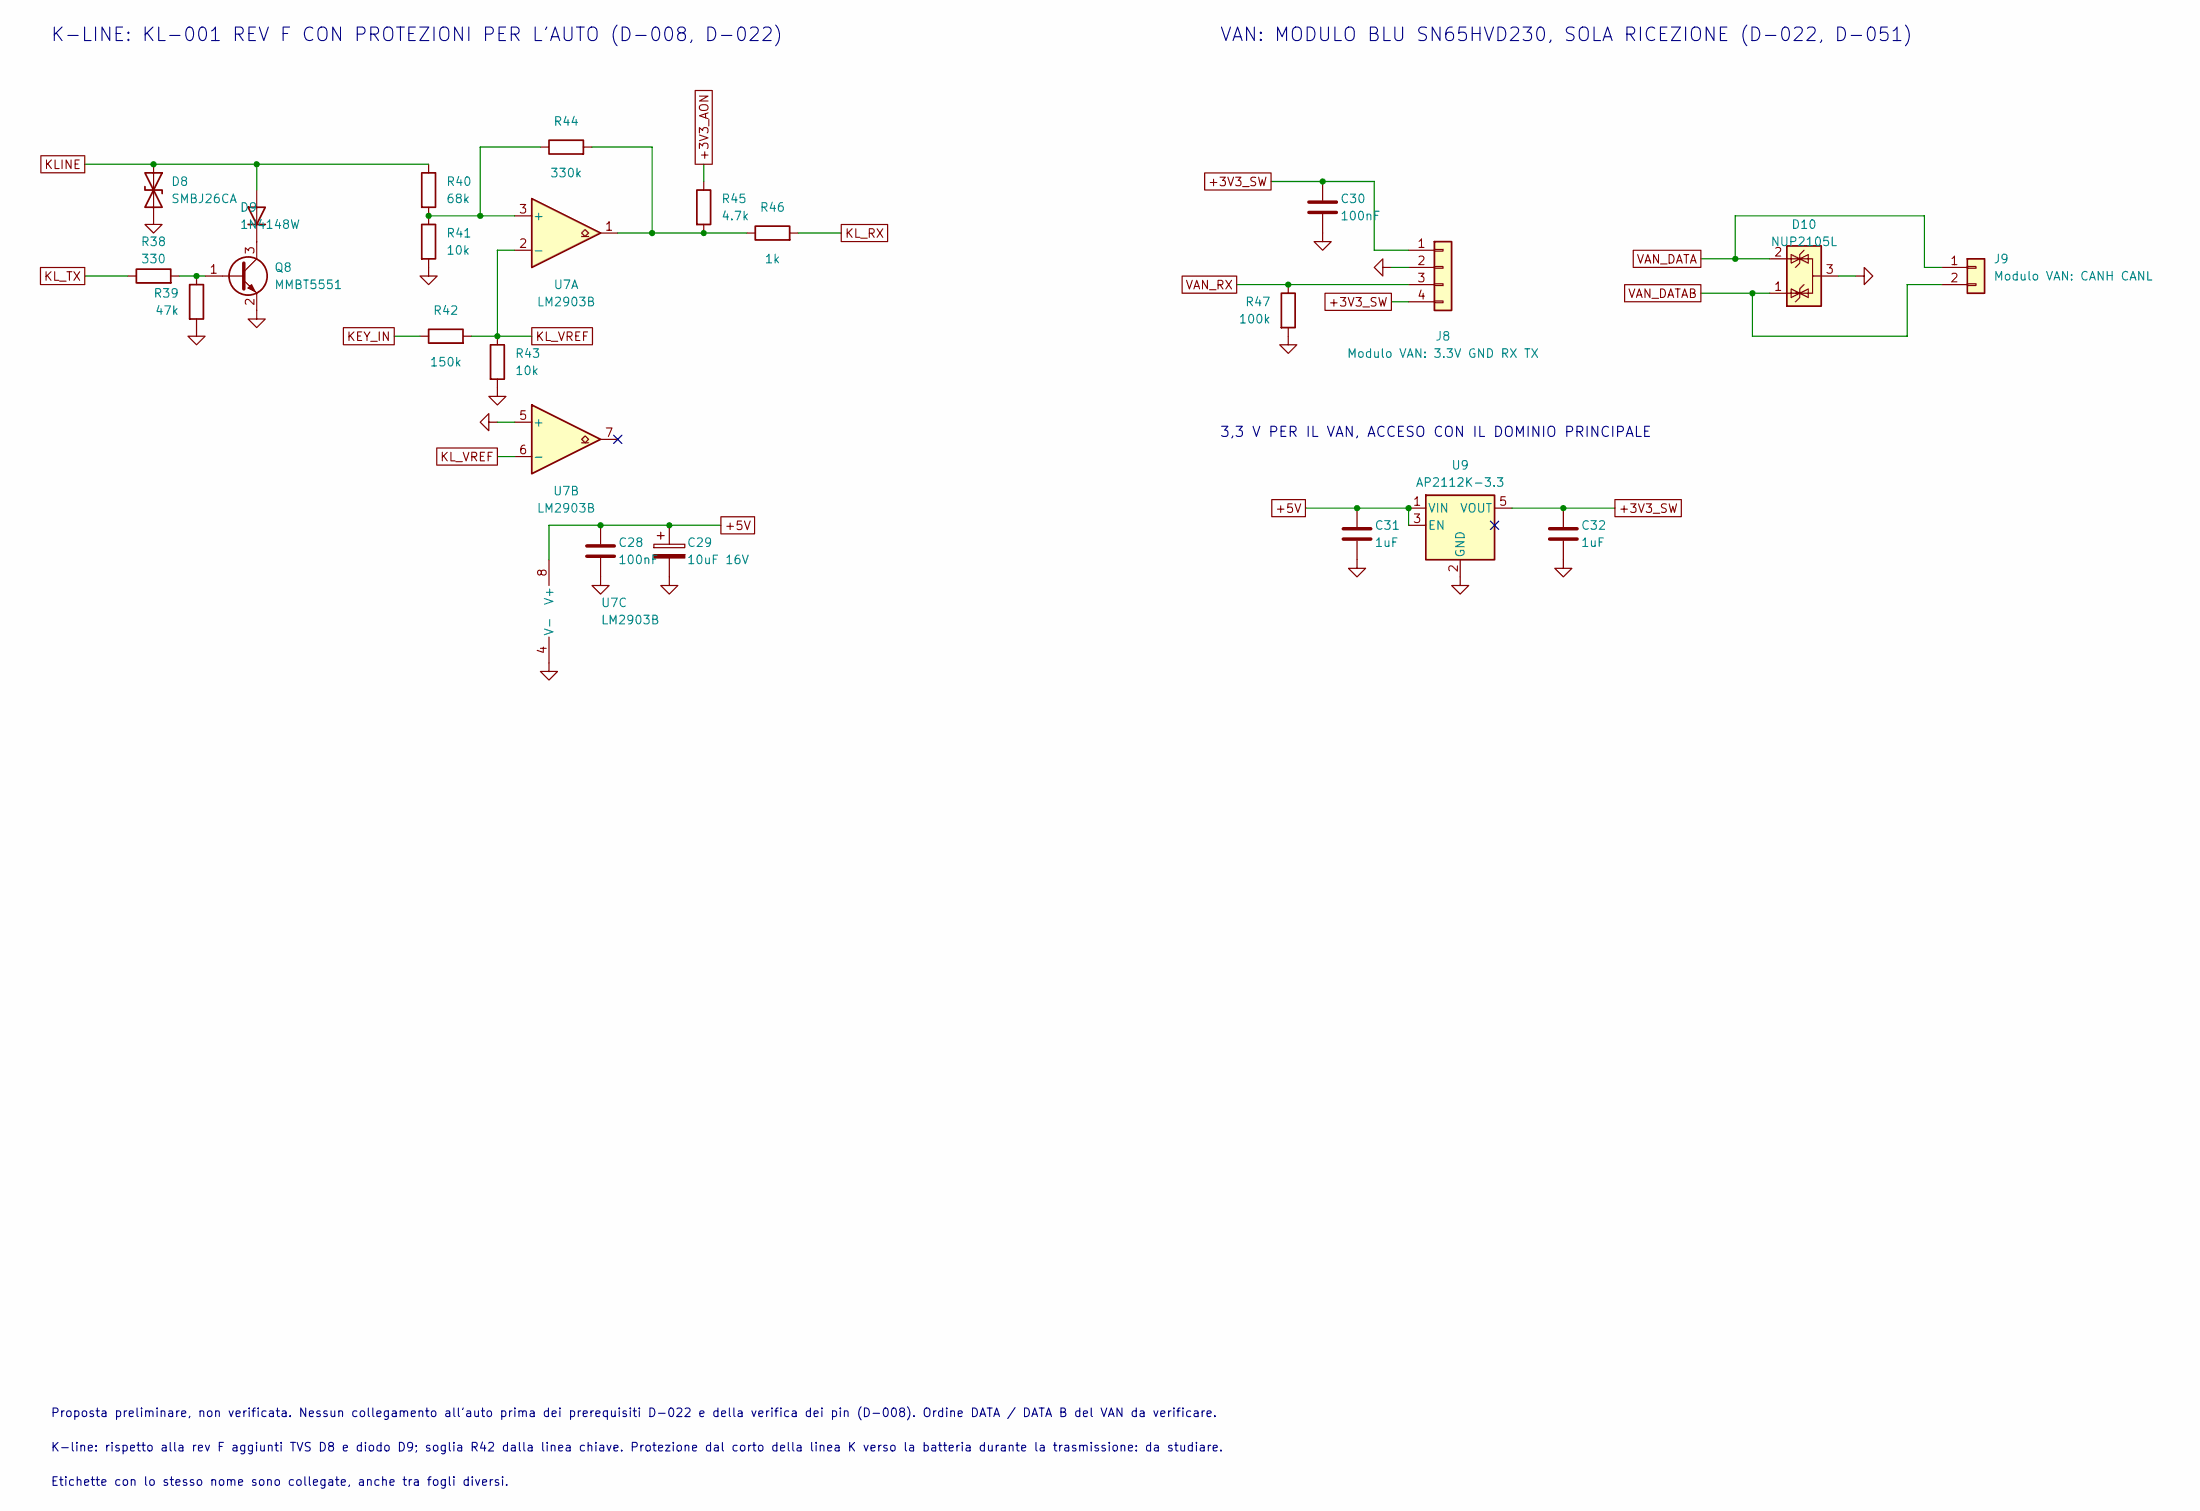
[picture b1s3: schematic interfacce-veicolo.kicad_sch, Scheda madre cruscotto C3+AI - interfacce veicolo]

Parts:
C28, C30: 100nF; C_0805_2012Metric_Pad1.18x1.45mm_HandSolder
C29: 10uF 16V; CP_Elec_4x5.4
C31, C32: 1uF; C_0805_2012Metric_Pad1.18x1.45mm_HandSolder
D8: SMBJ26CA; D_SMB
D9: 1N4148W; D_SOD-123
D10: NUP2105L; SOT-23
J8: Modulo VAN: 3.3V GND RX TX; Modulo_VAN_SN65HVD230
J9: Modulo VAN: CANH CANL; SolderWire-0.127sqmm_1x02_P3.7mm_D0.48mm_OD1mm
Q8: MMBT5551; SOT-23
R38: 330; R_0805_2012Metric_Pad1.20x1.40mm_HandSolder
R39: 47k; R_0805_2012Metric_Pad1.20x1.40mm_HandSolder
R40: 68k; R_0805_2012Metric_Pad1.20x1.40mm_HandSolder
R41, R43: 10k; R_0805_2012Metric_Pad1.20x1.40mm_HandSolder
R42: 150k; R_0805_2012Metric_Pad1.20x1.40mm_HandSolder
R44: 330k; R_0805_2012Metric_Pad1.20x1.40mm_HandSolder
R45: 4.7k; R_0805_2012Metric_Pad1.20x1.40mm_HandSolder
R46: 1k; R_0805_2012Metric_Pad1.20x1.40mm_HandSolder
R47: 100k; R_0805_2012Metric_Pad1.20x1.40mm_HandSolder
U7: LM2903B; SOIC-8_3.9x4.9mm_P1.27mm
U9: AP2112K-3.3; SOT-23-5

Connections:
+3V3_AON: R45.1; also elsewhere on the board
+3V3_SW: C30.1, C32.1, J8.1, J8.4, U9.5 (VOUT); also elsewhere on the board
+5V: C28.1, C29.1, C31.1, U7.8 (V+), U9.1 (VIN), U9.3 (EN); also elsewhere on the board
GND: C28.2, C29.2, C30.2, C31.2, C32.2, D8.2 (A2), D10.3 (A), J8.2, Q8.2 (E), R39.2, R41.2, R43.2, R47.2, U7.4 (V-), U7.5 (+), U9.2 (GND); also elsewhere on the board
KEY_IN: R42.1; also elsewhere on the board
KLINE: D8.1 (A1), D9.2 (A), R40.1; also elsewhere on the board
KL_RX: R46.2; also elsewhere on the board
KL_TX: R38.1; also elsewhere on the board
KL_VREF: R42.2, R43.1, U7.2 (-), U7.6 (-)
unnamed: D9.1 (K), Q8.3 (C)
unnamed: Q8.1 (B), R38.2, R39.1
unnamed: R44.2, R45.2, R46.1, U7.1
unnamed: R40.2, R41.1, R44.1, U7.3 (+)
VAN_DATA: D10.2 (K), J9.1; also elsewhere on the board
VAN_DATAB: D10.1 (K), J9.2; also elsewhere on the board
VAN_RX: J8.3, R47.1; also elsewhere on the board

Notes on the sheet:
K-LINE: KL-001 REV F CON PROTEZIONI PER L'AUTO (D-008, D-022)
VAN: MODULO BLU SN65HVD230, SOLA RICEZIONE (D-022, D-051)
3,3 V PER IL VAN, ACCESO CON IL DOMINIO PRINCIPALE
Proposta preliminare, non verificata. Nessun collegamento all'auto prima dei prerequisiti D-022 e della verifica dei pin (D-008). Ordine DATA / DATA B del VAN da verificare.
K-line: rispetto alla rev F aggiunti TVS D8 e diodo D9; soglia R42 dalla linea chiave. Protezione dal corto della linea K verso la batteria durante la trasmissione: da studiare.
Etichette con lo stesso nome sono collegate, anche tra fogli diversi.
